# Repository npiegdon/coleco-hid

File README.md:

# ColecoHID: A USB adapter for the ColecoVision Roller Controller

I was able to find lots of ColecoVision-to-USB adapters, but none that supported the Roller Controller accessory.

**[Watch the video!](https://youtu.be/rTsxjneUAzo)**

The Roller Controller connects to the ColecoVision console using controller ports 1 and 2 simultaneously, which means a single-port USB adapter won't work.  The Roller Controller also requires a bit of extra power using a curious pass-through cable with a proprietary connector.  ColecoHID solves both problems in one compact adapter.

## Features

- Fully HID-compliant USB 2.0 game pad inputs, so it should work on any operating system without a driver.
- A toggle switch for "mouse mode" which combines the quadrature axes from both controller ports into an HID-compliant mouse input.  (This lets you use the ColecoVision Roller Controller as a track ball mouse.  This is also required for playing some games with the Roller Controller in emulators like [MESS](http://www.mess.org/).)         
- Supports 2x standard ColecoVision controllers, 2x Super Action Controllers (including their wheels), or the Roller Controller.
- Additional (untested!) support most likely includes standard Atari joysticks and Sega Genesis controllers.

## Design Notes

The final design uses an Atmel [ATmega32U2](http://www.atmel.com/devices/ATMEGA32U2.aspx) which supports full speed USB 2.0.  A 3D-printed enclosure replicates the Roller Controller's proprietary power connector.  Conveniently, it only requires a small bit of current at 5V, so it's able to use USB bus power directly.

The majority of the initial technical info for the project came from [Deathskull Labs](http://arcarc.xmission.com/Web%20Archives/Deathskull%20(May-2006)/games/tech/index.html).  Thanks guys!

Printing [the case](http://www.shapeways.com/product/W9YRKPY3Y) at Shapeways in "White Strong and Flexible, Polished" created a nice result.  (The current case has a small deficiency: while the retaining clips hold things in place along two dimensions, the top cover has a tendency to slide forward and backward.  This makes it a little easier to open, so maybe it's a feature!)    

The enclosure is made to accept crimped Molex pins, which seem to work well with the original ColecoVision hardware.  I bought two sizes (14-20 and 18-22 gauge) but my notes are unclear which ended up being the correct size.  (Sorry!)

This project included a lot of firsts for me: my first USB device, my first circuit board layout, my first 3D case design.  So, expect some rough edges (like the sliding top of the case).  That said, the code can serve as a simple HID-USB example project using the [LUFA USB library](http://www.lufa-lib.org).

I had a set of three PCBs made from the gerber files by [OSH Park](https://oshpark.com/) for about $12.

The firmware can be built using Atmel Studio.  I programmed the ATmega32U2 using an [AVRISP mkII](http://www.atmel.com/tools/AVRISPMKII.aspx).  (The board includes the six pin programming header for the AVRISP.)

The rest of the components were from [DigiKey](http://www.digikey.com/).  See the BOM below for the full list, but it ends up being somewhere in the neighborhood of $15 for single-unit quantities of all the parts. 

The PCB uses some surface mount components.  You can print a stencil from [OSH Stencils](https://www.oshstencils.com/) (using the same gerber files) for about $5.  That stencil, some solder paste, a pair of tweezers, and a hotplate is all it took to re-flow solder the board.  None of the components are very fine-pitch, so you could probably get away with using a soldering iron or hot air tool instead. 

# Bill of Materials

<table>
    <tr>
        <td>Item</td>
		<td>Digikey part number</td>
		<td>Qty Required</td>
    </tr>
    <tr>
        <td>ATMega32U2-AU</td>
        <td>ATMEGA32U2-AU-ND</td>
        <td>1</td>
    </tr>
    <tr>
        <td>DSUB 9</td>
        <td>609-4002-ND</td>
        <td>2</td>
    </tr>
    <tr>
        <td>16.0 MHz 4-pad crystal, 2.5x2 mm</td>
        <td>644-1059-1-ND</td>
        <td>1</td>
    </tr>
    <tr>
        <td>USB B connector</td>
        <td>WM17113-ND</td>
        <td>1</td>
    </tr>
    <tr>
        <td>mini SPDT switch</td>
        <td>CKN9559-ND</td>
        <td>1</td>
    </tr>
    <tr>
        <td>6-pin programming header</td>
        <td>609-3210-ND</td>
        <td>1</td>
    </tr>
    <tr>
        <td>0603 1uF capacitor</td>
        <td>311-1446-1-ND</td>
        <td>5</td>
    </tr>
    <tr>
        <td>0603 10pF capacitor</td>
        <td>311-1058-1-ND</td>
        <td>2</td>
    </tr>
    <tr>
        <td>0603 22 resistor</td>
        <td>311-22.0HRCT-ND</td>
        <td>2</td>
    </tr>
    <tr>
        <td>0805 10k resistor</td>
        <td>311-10.0KCRCT-ND</td>
        <td>1</td>
    </tr>
    <tr>
        <td>Solder paste (leaded)</td>
        <td>KE1507-ND</td>
        <td></td>
    </tr>
    <tr>
        <td>ColecoHID PCB v1</td>
        <td>from OSH Park</td>
        <td>$12 for three</td>
    </tr>
    <tr>
        <td>Solider paste stencil</td>
        <td>from OSH Stencils</td>
        <td>$5</td>
    </tr>
    <tr>
        <td>Shapeways Enclosure</td>
        <td><a href="http://www.shapeways.com/product/W9YRKPY3Y">from Shapeways</a></td>
        <td>$21</td>
    </tr>
    <tr>
        <td>Molex (14-20 or 18-22) Gauge Pins 0.093"<br/>(I'm not sure which size, sorry!)</td>
        <td>from Amazon.com</td>
        <td>two male, two female</td>
    </tr>
    <tr>
        <td>Red / black hookup wire</td>
        <td></td>
        <td>a few inches</td>
    </tr>
</table>

## Future Work

- Use a micro-B USB connector instead of a full-size B connector.
- Push the USB port as far back onto the PCB as possible instead of having it dangling off the end, requiring a larger case.
- Strengthen the case where the Roller Controller power is plugged in.  It flexes a little too much when plugging and unplugging. 
- Compress the board layout a lot more.  The final case volume could trivially be half what it is today.
- Fix the sliding top half of the case by adding a couple more retention clips on the other axis.
- Create a software utility (and updated firmware) to allow user control of joystick and mouse configuration and sensitivity.

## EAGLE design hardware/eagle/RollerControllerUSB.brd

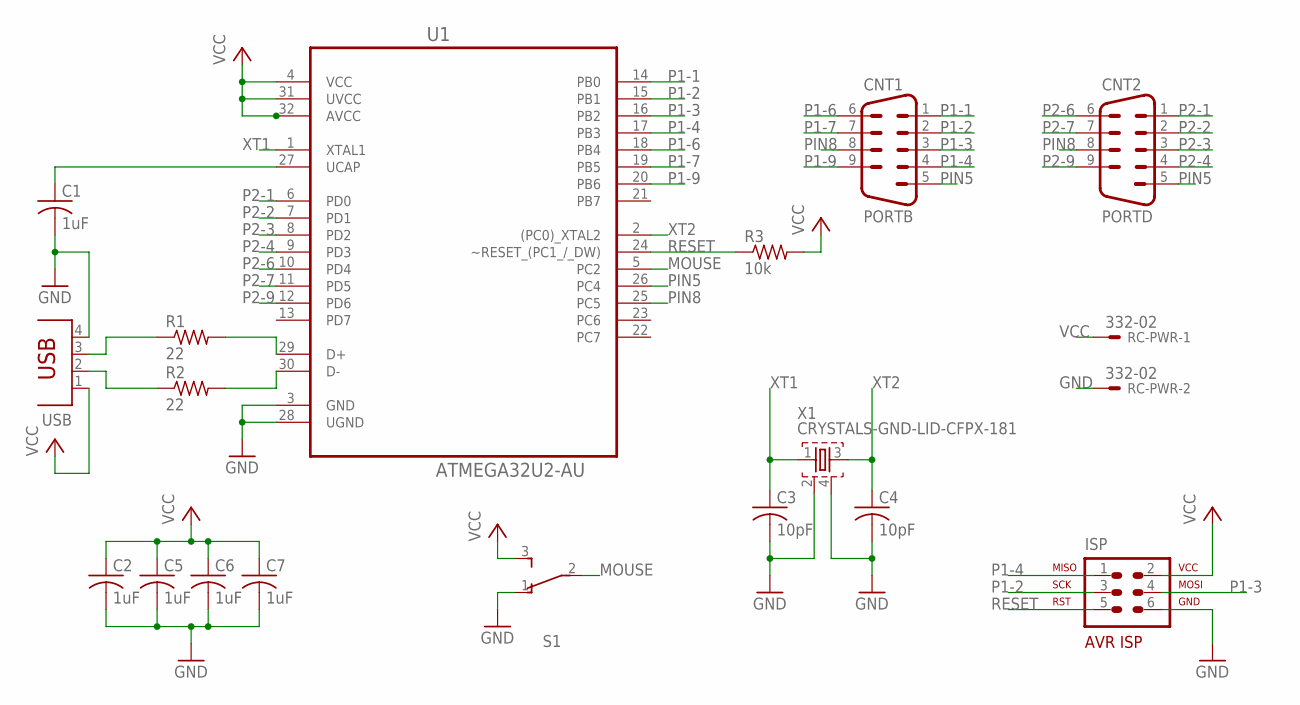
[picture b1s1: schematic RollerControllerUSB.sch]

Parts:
C1, C2, C5, C6, C7: 1uF; C0603
C3, C4: 10pF; C0603
CNT1: PORTB; M09HP
CNT2: PORTD; M09HP
ISP: AVR-ISP-6VERT; AVR-ISP-6
R1, R2: 22; R0603
R3: 10k; R0805
RC-PWR: 332-02
S1: OS102011MA1QN1
U1: ATMEGA32U2-AU; QFP80P900X900X120-32N
USB: PN61729
X1: CRYSTALS-GND-LID-CFPX-181; 2.5X2-4-PAD

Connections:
D_N: R2.2, U1.30 (D-)
D_P: R1.2, U1.29 (D+)
GND: C1.2, C2.2, C3.2, C4.2, C5.2, C6.2, C7.2, ISP.6, RC-PWR.2, S1.1 (O), U1.3 (GND), U1.28 (UGND), USB.4, X1.2, X1.4
MOUSE: S1.2, U1.5 (PC2)
unnamed: C1.1, U1.27 (UCAP)
P1-1: CNT1.1, U1.14 (PB0)
P1-2: CNT1.2, ISP.3, U1.15 (PB1)
P1-3: CNT1.3, ISP.4, U1.16 (PB2)
P1-4: CNT1.4, ISP.1, U1.17 (PB3)
P1-6: CNT1.6, U1.18 (PB4)
P1-7: CNT1.7, U1.19 (PB5)
P1-9: CNT1.9, U1.20 (PB6)
P2-1: CNT2.1, U1.6 (PD0)
P2-2: CNT2.2, U1.7 (PD1)
P2-3: CNT2.3, U1.8 (PD2)
P2-4: CNT2.4, U1.9 (PD3)
P2-6: CNT2.6, U1.10 (PD4)
P2-7: CNT2.7, U1.11 (PD5)
P2-9: CNT2.9, U1.12 (PD6)
PIN5: CNT1.5, CNT2.5, U1.26 (PC4)
PIN8: CNT1.8, CNT2.8, U1.25 (PC5)
RESET: ISP.5, R3.1, U1.24 (~RESET_(PC1_/_DW))
USB_N: R2.1, USB.2
USB_P: R1.1, USB.3
VCC: C2.1, C5.1, C6.1, C7.1, ISP.2, R3.2, RC-PWR.1, S1.3 (S), U1.4 (VCC), U1.31 (UVCC), U1.32 (AVCC), USB.1
XT1: C3.1, U1.1 (XTAL1), X1.1
XT2: C4.1, U1.2 ((PC0)_XTAL2), X1.3

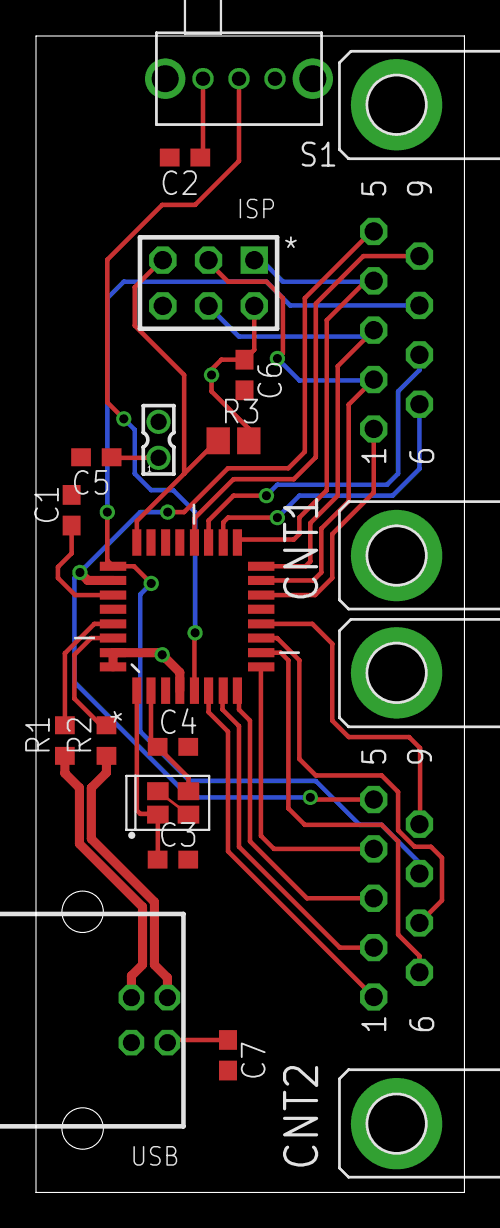
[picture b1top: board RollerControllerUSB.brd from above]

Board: 2 copper layers, 23.8 x 64.2 mm, 18 parts (0 on the bottom side), 27 nets.

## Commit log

2016-05-06 Add everything
